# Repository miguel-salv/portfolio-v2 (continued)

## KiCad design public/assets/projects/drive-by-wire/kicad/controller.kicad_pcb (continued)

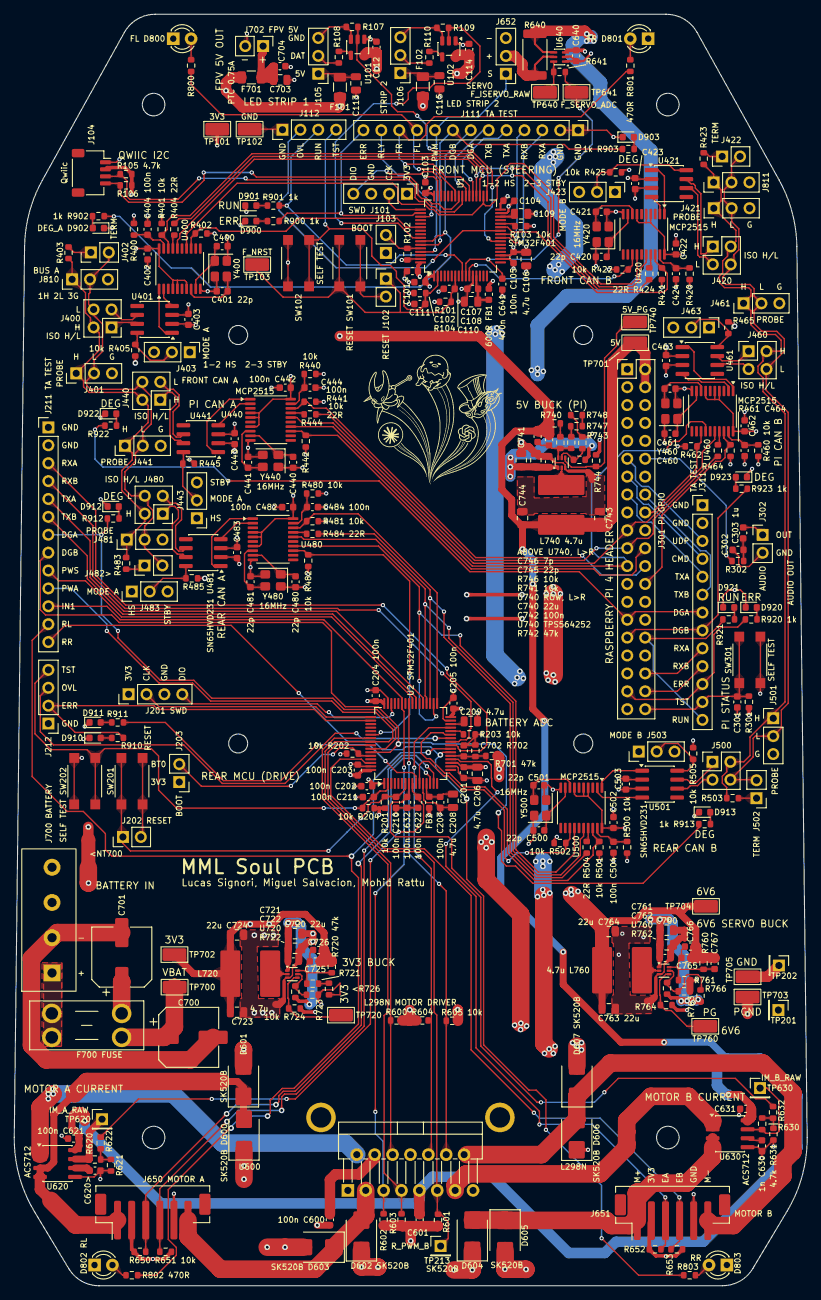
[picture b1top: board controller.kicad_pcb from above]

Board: 4 copper layers, 112.6 x 180.5 mm, 342 parts (0 on the bottom side), 216 nets.

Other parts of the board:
H1, H2, H3, H4: ChassisMount_3.2mm
H5, H6, H7, H8: PiMount_2.7mm

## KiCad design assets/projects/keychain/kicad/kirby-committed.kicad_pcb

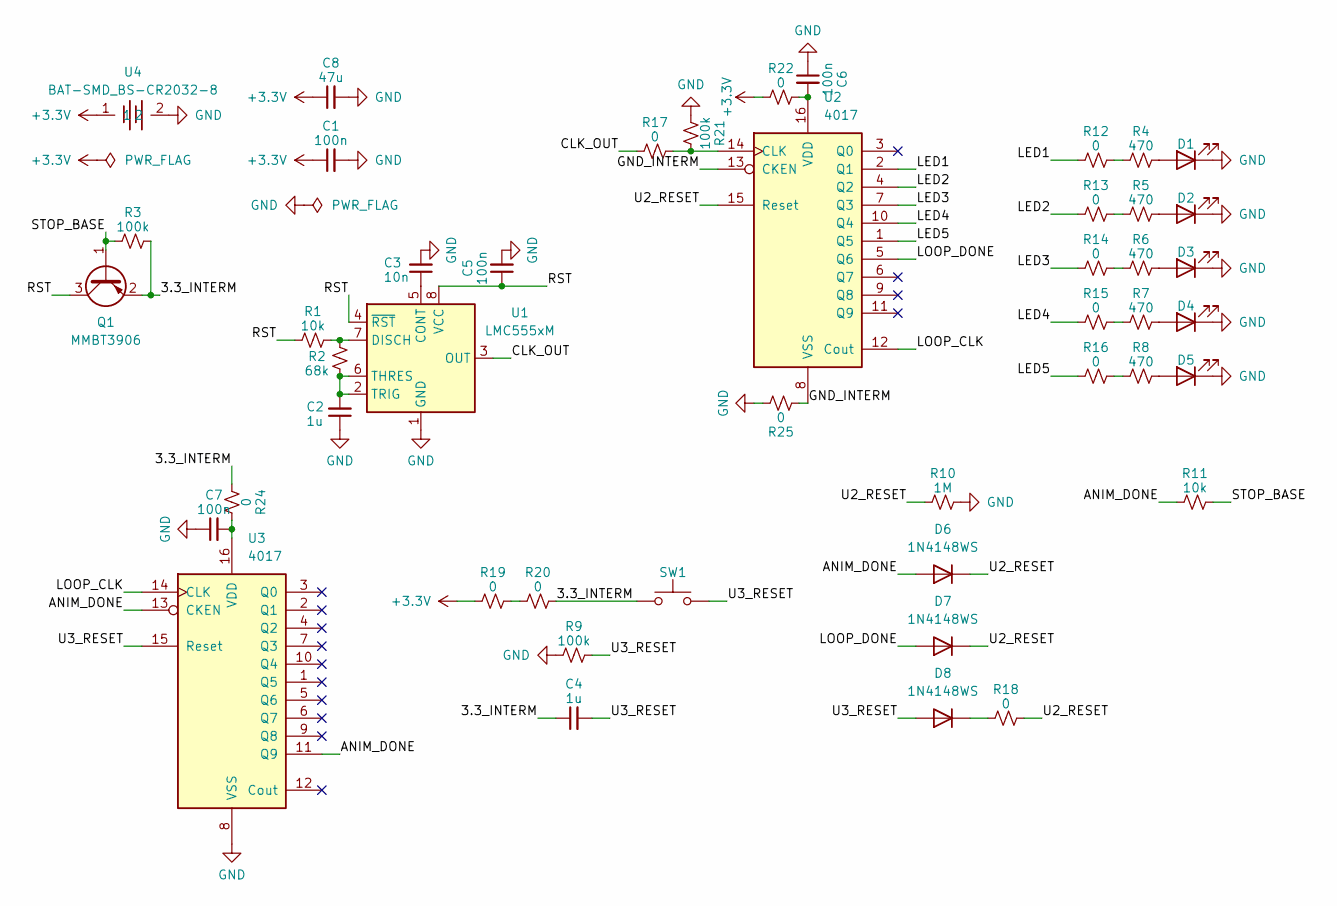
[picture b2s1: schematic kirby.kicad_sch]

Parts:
C1, C5, C6, C7: 100n; C_0805_2012Metric
C2, C4: 1u; C_0805_2012Metric
C3: 10n; C_0805_2012Metric
C8: 47u; C_1206_3216Metric
D1, D2, D3, D4, D5: LED-SMD_3P-L3_2-W1_0-RD_TJ-S3210SW5TGLC9Y-A5_C273628; LCSC C273626
D6, D7, D8: 1N4148WS; D_SOD-323
Q1: MMBT3906; SOT23-3; LCSC C53444
R1, R11: 10k; R_0805_2012Metric
R2: 68k; R_0805_2012Metric
R3, R9, R21: 100k; R_0805_2012Metric
R4, R5, R6, R7, R8: 470; R_0805_2012Metric
R10: 1M; R_0805_2012Metric
R12, R13, R14, R15, R16, R17, R18, R19, R20, R22, R24, R25: 0; R_0805_2012Metric
SW1: SMD_12x12mm_h8.5mm; Push_SMD_12x12mm; Mfg Part# EG4904TR-ND; LCSC C18186481
U1: LMC555xM; SOIC-8_3.9x4.9mm_P1.27mm; LCSC C90760
U2, U3: 4017; SOIC-16_3.9x9.9mm_P1.27mm; LCSC C148206
U4: BAT-SMD_BS-CR2032-8; BAT-SMD_BS-CR2032-8_BS-CR2032-8_C7498149; LCSC C7498149

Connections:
+3.3V: C1.1, C8.1, R19.1, R22.1, U4.1
/3.3_INTERM: C4.1, Q1.2 (E), R3.2, R20.2, R24.1, SW1.1
/ANIM_DONE: D6.2 (A), R11.1, U3.11 (Q9), U3.13 (CKEN)
/CLK_OUT: R17.1, U1.3 (OUT)
/GND_INTERM: R25.1, U2.8 (VSS), U2.13 (CKEN)
/LED1: R12.1, U2.2 (Q1)
/LED2: R13.1, U2.4 (Q2)
/LED3: R14.1, U2.7 (Q3)
/LED4: R15.1, U2.10 (Q4)
/LED5: R16.1, U2.1 (Q5)
/LOOP_CLK: U2.12 (Cout), U3.14 (CLK)
/LOOP_DONE: D7.2 (A), U2.5 (Q6)
/RST: C5.1, Q1.3 (C), R1.1, U1.4 (~RST), U1.8 (VCC)
/STOP_BASE: Q1.1 (B), R3.1, R11.2
/U2_RESET: D6.1 (K), D7.1 (K), R10.1, R18.2, U2.15 (Reset)
/U3_RESET: C4.2, D8.2 (A), R9.1, SW1.2, U3.15 (Reset)
GND: C1.2, C2.1, C3.2, C5.2, C6.1, C7.1, C8.2, D1.1 (K), D2.1 (K), D3.1 (K), D4.1 (K), D5.1 (K), R9.2, R10.2, R21.1, R25.2, U1.1 (GND), U3.8 (VSS), U4.2
unnamed: D1.2 (A), R4.2
unnamed: D2.2 (A), R5.2
unnamed: D3.2 (A), R6.2
unnamed: D4.2 (A), R7.2
unnamed: D5.2 (A), R8.2
unnamed: D8.1 (K), R18.1
unnamed: R4.1, R12.2
unnamed: R5.1, R13.2
unnamed: R6.1, R14.2
unnamed: R7.1, R15.2
unnamed: R8.1, R16.2
unnamed: R19.2, R20.1
unnamed: C3.1, U1.5 (CONT)
unnamed: R1.2, R2.2, U1.7 (DISCH)
unnamed: C2.2, R2.1, U1.2 (TRIG), U1.6 (THRES)
unnamed: R17.2, R21.2, U2.14 (CLK)
unnamed: C6.2, R22.2, U2.16 (VDD)
unnamed: C7.2, R24.2, U3.16 (VDD)

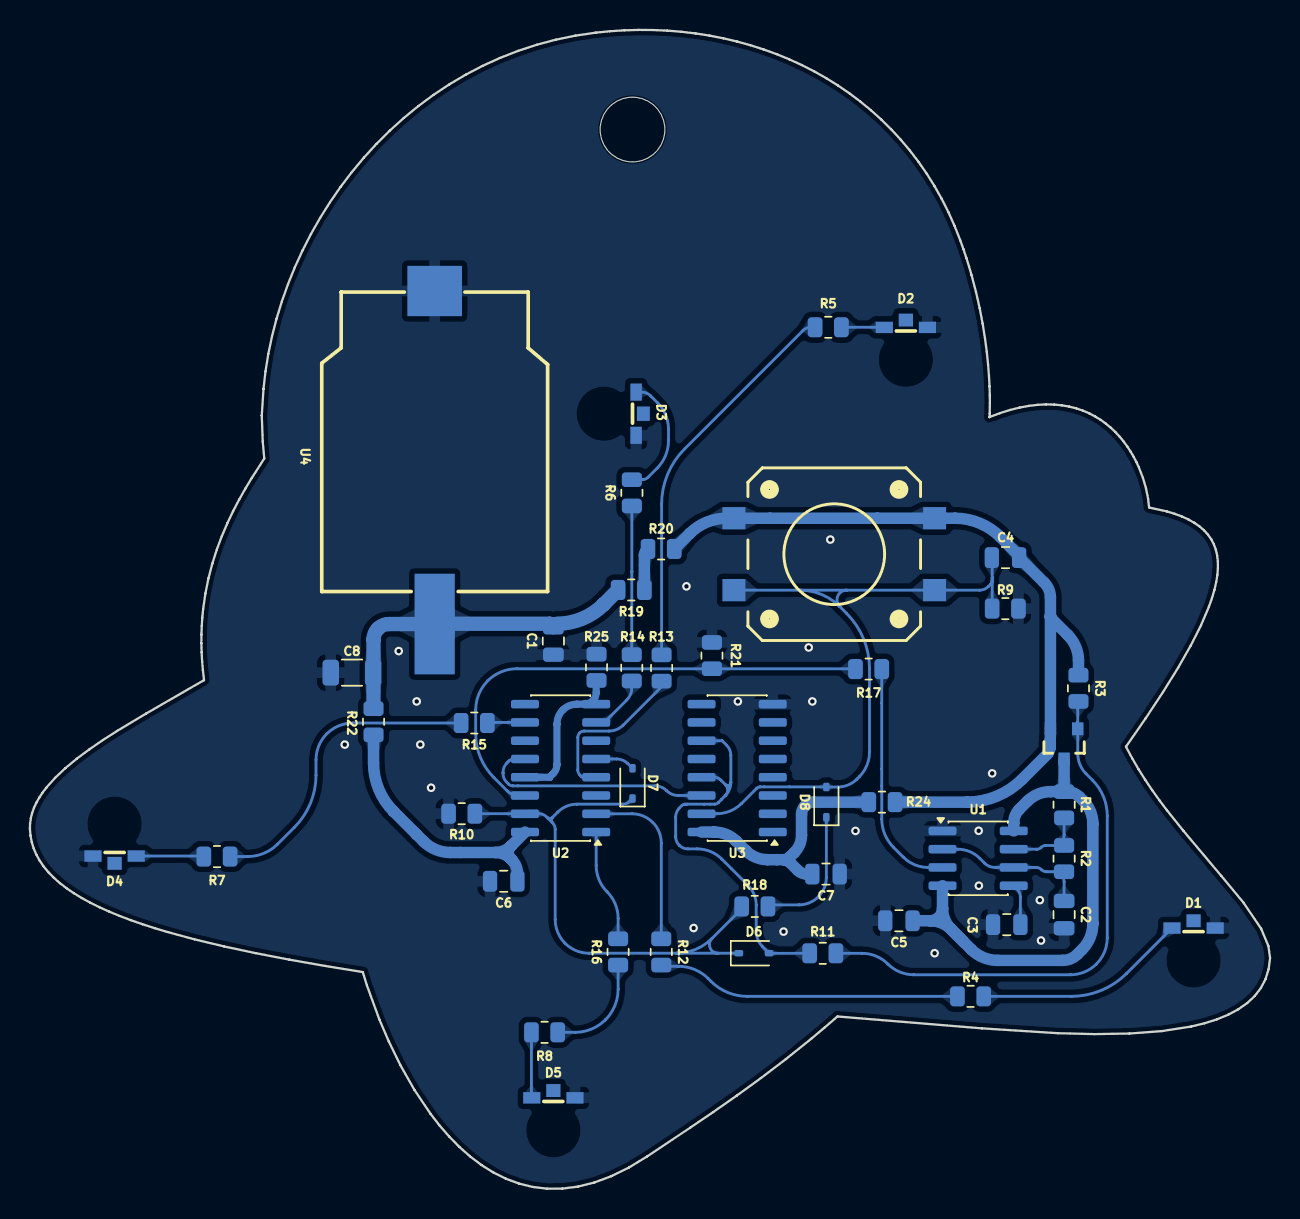
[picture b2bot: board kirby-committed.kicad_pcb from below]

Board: 2 copper layers, 86.2 x 80.5 mm, 46 parts (46 on the bottom side), 35 nets.
